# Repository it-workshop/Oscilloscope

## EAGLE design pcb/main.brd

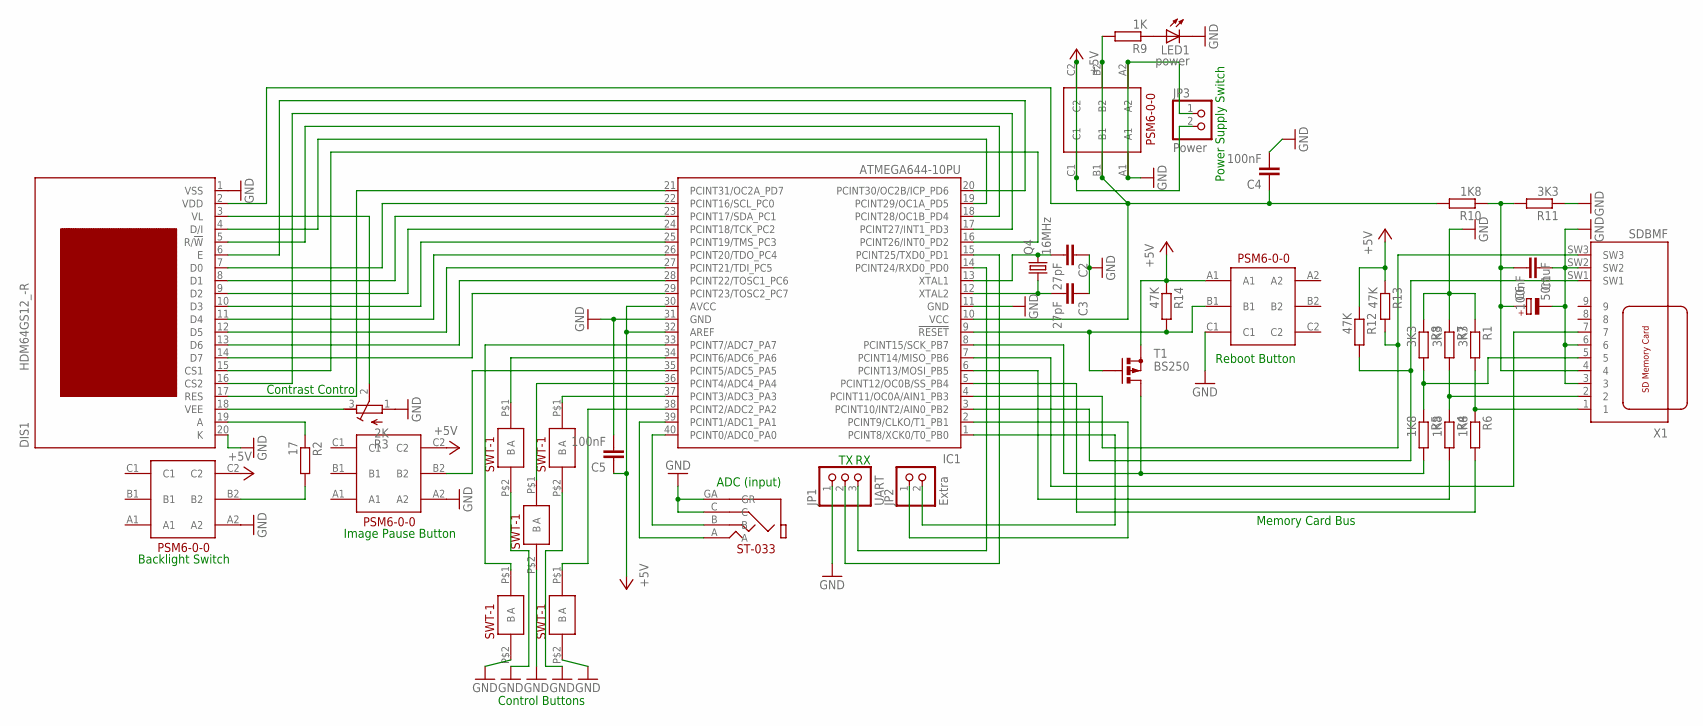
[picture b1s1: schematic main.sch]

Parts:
C1, C4, C5: 100nF; C050-075X075
C2, C3: 27pF; C050-075X075
C6: 50muF; E5-13
DIS1: HDM64GS12_-R
IC1: ATMEGA644-10PU; DIL40
JP1: UART; 1X03
JP2: Extra; 1X02
JP3: Power; 1X02
LED1: power; LED3MM
Q4: 16MHz; HC49U-V
R1, R7, R8, R11: 3K3; 0204/7
R2: 17; P0817/22
R3: 2K; RTRIM4G/J
R4, R5, R6, R10: 1K8; 0204/7
R9: 1K; 0204/7
R12, R13, R14: 47K; 0204/7
T1: BS250; SOT54E
U$1_TOP: TOP; SWT-1
U$2_RIGHT: RIGHT; SWT-1
U$3_LEFT: LEFT; SWT-1
U$4_BOTTOM: BOTTOM; SWT-1
U$5_CENTER: CENTER; SWT-1
U$6_BACKLIGHT, U$6_PAUSE: pause; PSM6-0-0
U$7_POWER: power; PSM6-0-0
U$8_REBOOT: reboot; PSM6-0-0
U$11: ST-033
X1: SDBMF; SDBMF-009XXBXX2

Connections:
+5V: C5.1, IC1.30 (AVCC), IC1.32 (AREF), JP3.2, R12.1, R13.1, R14.1, T1.S, U$6_BACKLIGHT.C2, U$6_PAUSE.C2, U$7_POWER.C1, U$7_POWER.C2, U$8_REBOOT.A1
GND: C1.1, C2.1, C3.1, C4.2, C5.2, C6.-, DIS1.1 (VSS), DIS1.20 (K), IC1.11 (GND), IC1.31 (GND), JP1.1, JP3.1, LED1.K (C), R1.1, R3.1 (E), R7.1, R8.1, R11.1, U$1_TOP.P$2 (B), U$2_RIGHT.P$2 (B), U$3_LEFT.P$2 (B), U$4_BOTTOM.P$2 (B), U$5_CENTER.P$2 (B), U$6_BACKLIGHT.A2, U$6_PAUSE.A2, U$7_POWER.A1, U$7_POWER.A2, U$8_REBOOT.C1, U$11.C, U$11.GA (GR), X1.3, X1.6, X1.SW2
unnamed: DIS1.13 (D6), IC1.28 (PCINT22/TOSC1_PC6)
unnamed: C2.2, IC1.13 (XTAL1), Q4.2
unnamed: DIS1.8 (D1), IC1.23 (PCINT17/SDA_PC1)
unnamed: DIS1.9 (D2), IC1.24 (PCINT18/TCK_PC2)
unnamed: DIS1.10 (D3), IC1.25 (PCINT19/TMS_PC3)
unnamed: DIS1.11 (D4), IC1.26 (PCINT20/TDO_PC4)
unnamed: DIS1.12 (D5), IC1.27 (PCINT21/TDI_PC5)
unnamed: IC1.36 (PCINT4/ADC4_PA4), U$3_LEFT.P$1 (A)
unnamed: DIS1.14 (D7), IC1.29 (PCINT23/TOSC2_PC7)
unnamed: IC1.5 (PCINT12/OC0B/SS_PB4), R6.2
unnamed: DIS1.3 (VL), R3.2 (S)
unnamed: DIS1.19 (A), R2.1
unnamed: LED1.A, R9.1
unnamed: DIS1.16 (CS2), IC1.17 (PCINT27/INT1_PD3)
unnamed: DIS1.5 (R/!W), IC1.18 (PCINT28/OC1B_PD4)
unnamed: DIS1.4 (D/I), IC1.19 (PCINT29/OC1A_PD5)
unnamed: DIS1.15 (CS1), IC1.16 (PCINT26/INT0_PD2)
unnamed: DIS1.17 (RES), IC1.21 (PCINT31/OC2A_PD7)
unnamed: IC1.6 (PCINT13/MOSI_PB5), R4.2
unnamed: DIS1.6 (E), IC1.20 (PCINT30/OC2B/ICP_PD6)
unnamed: IC1.4 (PCINT11/OC0A/AIN1_PB3), R13.2, X1.SW3
unnamed: R1.2, R6.1, X1.1
unnamed: R4.1, R7.2, X1.2
unnamed: R5.1, R8.2, X1.5
unnamed: IC1.39 (PCINT1/ADC1_PA1), U$11.A
unnamed: DIS1.7 (D0), IC1.22 (PCINT16/SCL_PC0)
unnamed: IC1.9 (!RESET), R14.2, T1.G, U$8_REBOOT.B1
unnamed: C3.2, IC1.12 (XTAL2), Q4.1
unnamed: IC1.34 (PCINT6/ADC6_PA6), U$1_TOP.P$1 (A)
unnamed: IC1.37 (PCINT3/ADC3_PA3), U$2_RIGHT.P$1 (A)
unnamed: IC1.15 (PCINT25/TXD0_PD1), JP1.2
unnamed: IC1.33 (PCINT7/ADC7_PA7), U$4_BOTTOM.P$1 (A)
unnamed: IC1.38 (PCINT2/ADC2_PA2), U$5_CENTER.P$1 (A)
unnamed: IC1.40 (PCINT0/ADC0_PA0), U$11.B
unnamed: IC1.14 (PCINT24/RXD0_PD0), JP1.3
unnamed: IC1.35 (PCINT5/ADC5_PA5), U$6_PAUSE.B2
unnamed: DIS1.18 (VEE), R3.3 (A)
unnamed: C1.2, C6.+, R10.1, R11.2, X1.4
unnamed: IC1.7 (PCINT14/MISO_PB6), X1.7
unnamed: IC1.3 (PCINT10/INT2/AIN0_PB2), R12.2, X1.SW1
unnamed: R2.2, U$6_BACKLIGHT.B2
unnamed: C4.1, DIS1.2 (VDD), IC1.10 (VCC), R9.2, R10.2, U$7_POWER.B1, U$7_POWER.B2
unnamed: IC1.8 (PCINT15/SCK_PB7), R5.2, T1.D
unnamed: IC1.2 (PCINT9/CLKO/T1_PB1), JP2.1
unnamed: IC1.1 (PCINT8/XCK0/T0_PB0), JP2.2

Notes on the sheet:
ADC (input)
Power Supply Switch
Image Pause Button
Reboot Button
Control Buttons
Memory Card Bus
Backlight Switch
Contrast Control

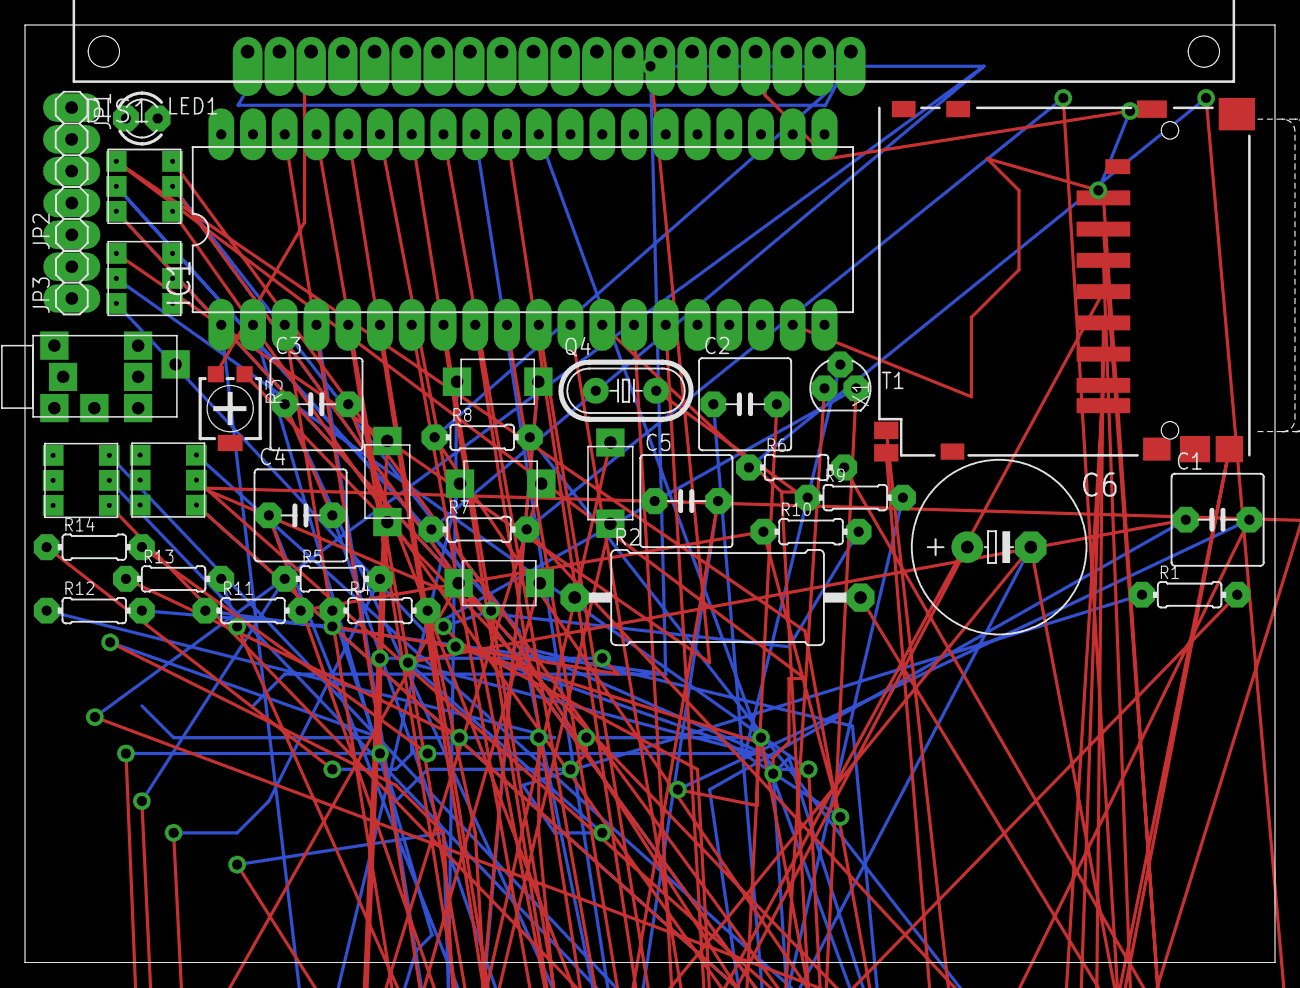
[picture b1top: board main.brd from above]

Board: 2 copper layers, 100.0 x 75.0 mm, 39 parts (0 on the bottom side), 47 nets.

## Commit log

2011-08-20 * Fixed Delay
2011-08-21 * "stable picture" by matching new data to prev. array * fixed lcd_num_from_right: now its drawing zero
2011-08-22 * sinal&menu * spectrum x and y scale * xy fixed * main draw code separated into functions
2011-08-24 * PC (UART) working - beta
2011-08-30 * code divided into files * MODE_UART working * MODE_UART_BUF still not working.
2011-09-15 * new menu * symbols: working with files
2011-09-18 * trigger values * adc interrupt: abs fixed
2011-09-23 * Extended documentation
2011-09-23 * signal_type: lines/dots
2011-09-24 * lcd_read(), lcd_pixel_share(), draw_signal():lines, fixed
2011-09-24 * lcd clear
2011-10-01 * generator * adc frequency is always fast, so dfreq (max) is 100kHz * voltage mode
2011-10-01 * generator interrupt * uart
2011-10-02 * &, @ symols * tzoom, vzoom, vpos
2011-10-16 * saw generator * desktop application supports trigger setup
2011-10-22 * adc_check works * better desktop interface
2011-10-22 * input selection in desktop application
2012-04-18 * PCB
2012-04-19 * device field in desktop application * desktop application works in QT 4.8.0
2012-04-19 * symbols fixed
2012-04-19 * theses (.doc) * indentation
2012-04-19 * indentation
2012-04-20 * desktop interface
2013-03-08 gitignore
2013-03-08 multiple DAC
2013-03-08 get_values, multiple DAC
2013-03-08 get_values DAC_N fix
2014-02-12 qt code project
2014-02-12 build fix
2014-02-12 fixed desktop&avr build
2014-12-07 trash
